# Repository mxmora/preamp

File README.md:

# preamp
Guitar buffer preamp

Added buffer input front end
Added more mounting holes

Version 1.1.4 only has the channel A clean section.
Version 1.1.4 has been built and tested and works with no error. Four minor errors were corrected and new boards were made.

Added Distortion Section
changed version to 1.2.0

This now has an A/B section A for clean and B for Lead Channel. 

Added LED for channel B indicator.

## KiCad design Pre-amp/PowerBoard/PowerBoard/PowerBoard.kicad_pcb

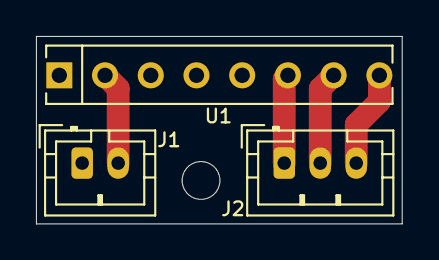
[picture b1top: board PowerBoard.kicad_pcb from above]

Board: 2 copper layers, 20.3 x 10.4 mm, 4 parts (0 on the bottom side), 5 nets.

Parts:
H1: MountingHole; MountingHole_2.1mm
J1: Conn_01x02_Male; JST_PH_B2B-PH-K_1x02_P2.00mm_Vertical
J2: Conn_01x03_Male; JST_PH_B3B-PH-K_1x03_P2.00mm_Vertical
U1: DPAN02; SIP-8_19x3mm_P2.54mm

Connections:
+9V: J1.2, U1.2
+15V: J2.1, U1.6
-15V: J2.3, U1.8
GND: J1.1, U1.1
unnamed: J2.2, U1.7

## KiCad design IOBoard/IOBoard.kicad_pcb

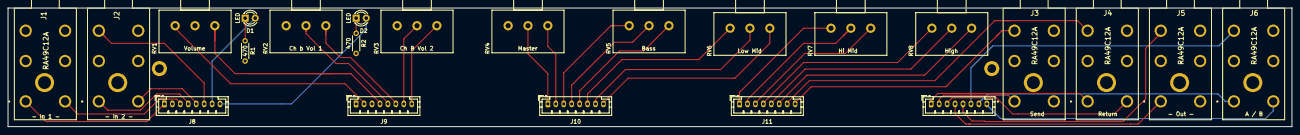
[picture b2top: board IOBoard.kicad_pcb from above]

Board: 2 copper layers, 323.2 x 29.8 mm, 25 parts (0 on the bottom side), 40 nets.

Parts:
D1, D2: LED; LED_D3.0mm
H1, H2: MountingHole_Pad; MountingHole_2.2mm_M2_DIN965_Pad
J1, J2, J3, J4, J5, J6: RA49C12A; RA49C14B
J7, J8, J9, J10, J11: Conn_01x08_Male; JST_PH_B8B-PH-K_1x08_P2.00mm_Vertical
R1, R2: 470; R_Axial_DIN0204_L3.6mm_D1.6mm_P5.08mm_Horizontal
RV1: Volume; Potentiometer_Alps_RK163_Single_Horizontal
RV2: Ch b Vol 1; Potentiometer_Alps_RK163_Single_Horizontal
RV3: Ch B Vol 2; Potentiometer_Alps_RK163_Single_Horizontal
RV4: Master; Potentiometer_Alps_RK163_Single_Horizontal
RV5: Bass; Potentiometer_Alps_RK163_Single_Horizontal
RV6: Low Mid; Potentiometer_Alps_RK163_Single_Horizontal
RV7: Hi Mid; Potentiometer_Alps_RK163_Single_Horizontal
RV8: High; Potentiometer_Alps_RK163_Single_Horizontal

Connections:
GND: H1.1, H2.1, J1.5, J8.2, J9.3, R1.2, R2.2, RV1.2, RV2.3, RV3.3, RV4.3
unnamed: D1.1, R1.1
unnamed: D1.2, J8.7
unnamed: D2.1, R2.1
unnamed: D2.2, J8.8
unnamed: J1.1, J8.1
unnamed: J1.2, J8.3
unnamed: J2.1, J8.4
unnamed: J2.2, J8.5
unnamed: J2.5, J8.6
unnamed: J3.1, J7.2
unnamed: J4.1, J7.1
unnamed: J4.2, J7.3
unnamed: J5.1, J7.4
unnamed: J5.5, J7.5
unnamed: J6.1, J7.7
unnamed: J6.2, J7.8
unnamed: J6.5, J7.6
unnamed: J9.2, RV1.3
unnamed: J9.4, RV1.1
unnamed: J9.5, RV2.2
unnamed: J9.6, RV2.1
unnamed: J9.7, RV3.2
unnamed: J9.8, RV3.1
unnamed: J10.1, RV4.2
unnamed: J10.2, RV4.1
unnamed: J10.3, RV5.3
unnamed: J10.4, RV5.2
unnamed: J10.5, RV5.1
unnamed: J10.6, RV6.3
unnamed: J10.7, RV6.2
unnamed: J10.8, RV6.1
unnamed: J11.1, RV7.3
unnamed: J11.2, RV7.2
unnamed: J11.3, RV7.1
unnamed: J11.4, RV8.3
unnamed: J11.5, RV8.2
unnamed: J11.6, RV8.1
unnamed: J4.5, J11.7
unnamed: J3.5, J11.8

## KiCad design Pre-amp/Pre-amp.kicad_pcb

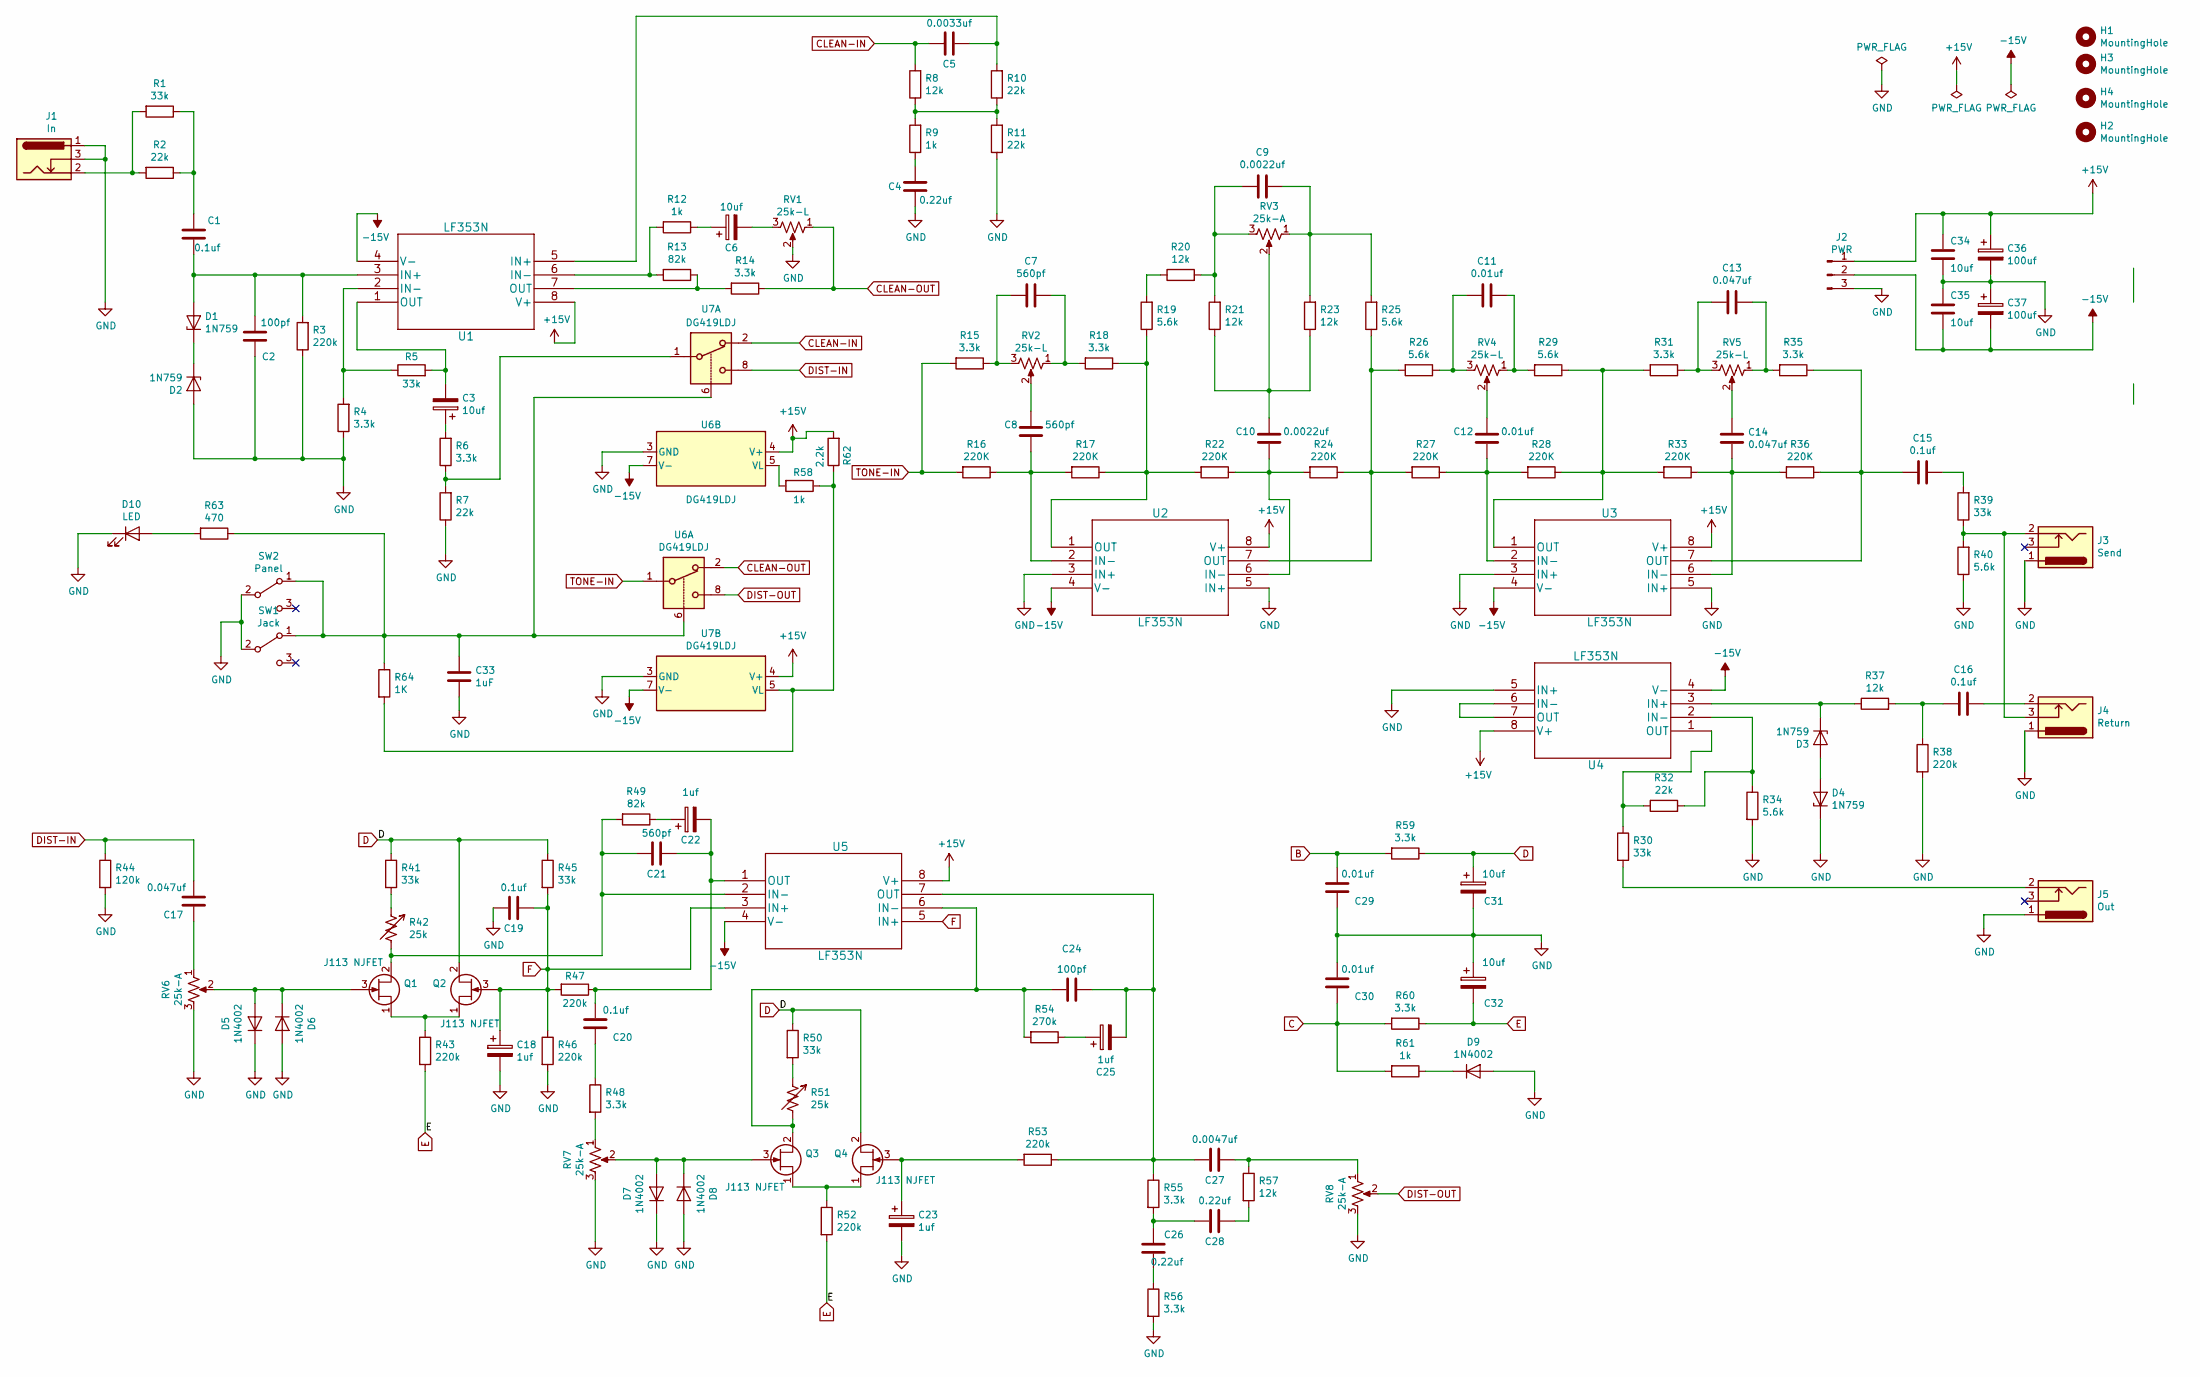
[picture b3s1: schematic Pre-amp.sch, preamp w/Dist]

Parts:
C1, C15, C16, C19, C20: 0.1uf; C_Disc_D3.8mm_W2.6mm_P2.50mm
C2, C24: 100pf; C_Disc_D3.8mm_W2.6mm_P2.50mm
C3, C6, C31, C32: 10uf; CP_Radial_D4.0mm_P1.50mm
C4, C26, C28: 0.22uf; C_Disc_D3.8mm_W2.6mm_P2.50mm
C5: 0.0033uf; C_Disc_D3.8mm_W2.6mm_P2.50mm
C7, C8, C21: 560pf; C_Disc_D3.8mm_W2.6mm_P2.50mm
C9, C10: 0.0022uf; C_Disc_D3.8mm_W2.6mm_P2.50mm
C11, C12, C29, C30: 0.01uf; C_Disc_D3.8mm_W2.6mm_P2.50mm
C13, C14, C17: 0.047uf; C_Disc_D3.8mm_W2.6mm_P2.50mm
C18, C22, C23, C25: 1uf; CP_Radial_D4.0mm_P1.50mm
C27: 0.0047uf; C_Disc_D3.8mm_W2.6mm_P2.50mm
C33: 1uF; C_Rect_L7.0mm_W2.0mm_P5.00mm
C34, C35: 10uf; C_Disc_D6.0mm_W2.5mm_P5.00mm
C36, C37: 100uf; CP_Radial_D8.0mm_P5.00mm
D1, D2, D3, D4: 1N759; D_DO-35_SOD27_P7.62mm_Horizontal
D5, D6, D7, D8, D9: 1N4002; D_DO-41_SOD81_P7.62mm_Horizontal
D10: LED; PinHeader_2x01_P2.00mm_Vertical
H1, H2, H3, H4: MountingHole; MountingHole_2.2mm_M2_DIN965_Pad
J1: In; PinHeader_1x03_P2.00mm_Vertical
J2: PWR; PinHeader_1x03_P2.00mm_Vertical
J3: Send; PinHeader_1x03_P2.00mm_Vertical
J4: Return; PinHeader_1x03_P2.00mm_Vertical
J5: Out; PinHeader_1x03_P2.00mm_Vertical
Q1, Q2, Q3, Q4: J113 NJFET; TO-92
R1, R5, R30, R39, R41, R45, R50: 33k; R_Axial_DIN0204_L3.6mm_D1.6mm_P5.08mm_Horizontal
R2, R7, R10, R11, R32: 22k; R_Axial_DIN0204_L3.6mm_D1.6mm_P5.08mm_Horizontal
R3, R38, R43, R46, R47, R52, R53: 220k; R_Axial_DIN0204_L3.6mm_D1.6mm_P5.08mm_Horizontal
R4, R6, R14, R15, R18, R31, R35, R48, R55, R56, R59, R60: 3.3k; R_Axial_DIN0204_L3.6mm_D1.6mm_P5.08mm_Horizontal
R8, R20, R21, R23, R37, R57: 12k; R_Axial_DIN0204_L3.6mm_D1.6mm_P5.08mm_Horizontal
R9, R12, R58, R61: 1k; R_Axial_DIN0204_L3.6mm_D1.6mm_P5.08mm_Horizontal
R13, R49: 82k; R_Axial_DIN0204_L3.6mm_D1.6mm_P5.08mm_Horizontal
R16, R17, R22, R24, R27, R28, R33, R36: 220K; R_Axial_DIN0204_L3.6mm_D1.6mm_P5.08mm_Horizontal
R19, R25, R26, R29, R34, R40: 5.6k; R_Axial_DIN0204_L3.6mm_D1.6mm_P5.08mm_Horizontal
R42, R51: 25k; Potentiometer_Bourns_3386F_Vertical
R44: 120k; R_Axial_DIN0204_L3.6mm_D1.6mm_P5.08mm_Horizontal
R54: 270k; R_Axial_DIN0204_L3.6mm_D1.6mm_P5.08mm_Horizontal
R62: 2.2k; R_Axial_DIN0204_L3.6mm_D1.6mm_P5.08mm_Horizontal
R63: 470; R_Axial_DIN0204_L3.6mm_D1.6mm_P5.08mm_Horizontal
R64: 1K; R_Axial_DIN0204_L3.6mm_D1.6mm_P5.08mm_Horizontal
RV1, RV2, RV4, RV5: 25k-L; Potentiometer_Alps_RK163_Single_Vertical
RV3, RV6, RV7, RV8: 25k-A; Potentiometer_Alps_RK163_Single_Vertical
SW1: Jack; Pin_Header_Straight_1x03_Pitch2.00mm
SW2: Panel; Pin_Header_Straight_1x03_Pitch2.00mm
U1, U2, U3, U4, U5: LF353N; DIP-8_W7.62mm_LongPads
U6, U7: DG419LDJ; DIP-8_W7.62mm_LongPads

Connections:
+15V: C34.1, C36.1, J2.1, R62.2, U1.8 (V+), U2.8 (V+), U3.8 (V+), U4.8 (V+), U5.8 (V+), U6.4 (V+), U7.4 (V+)
-15V: C35.2, C37.2, J2.2, U1.4 (V-), U2.4 (V-), U3.4 (V-), U4.4 (V-), U5.4 (V-), U6.7 (V-), U7.7 (V-)
B: C29.1, R59.2
C: C30.2, R60.2, R61.2
CLEAN-IN: C5.1, R8.2, U7.2
CLEAN-OUT: R14.1, RV1.1, U6.2
D: C31.1, Q2.2 (D), Q4.2 (D), R41.1, R45.1, R50.1, R59.1
DIST-IN: C17.1, R44.1, U7.8
DIST-OUT: RV8.2, U6.8
E: C32.2, R43.2, R52.2, R60.1
F: C18.1, C19.1, Q2.3 (G), R45.2, R46.1, R47.2, U5.3 (IN+), U5.5 (IN+)
GND: C2.1, C4.2, C18.2, C19.2, C23.2, C29.2, C30.1, C31.2, C32.1, C33.2, C34.2, C35.1, C36.2, C37.1, D2.2 (A), D4.1 (K), D5.1 (K), D6.2 (A), D7.1 (K), D8.2 (A), D9.2 (A), D10.1 (K), J1.1, J1.3, J2.3, J3.1, J4.1, J5.1, R3.1, R4.1, R7.1, R11.1, R34.2, R38.2, R40.1, R44.2, R46.2, R56.2, RV1.2, RV6.3, RV7.3, RV8.3, SW1.2 (B), SW2.2 (B), U2.3 (IN+), U2.5 (IN+), U3.3 (IN+), U3.5 (IN+), U4.5 (IN+), U6.3 (GND), U7.3 (GND)
unnamed: C1.1, C2.2, D1.2 (A), R3.2, U1.3 (IN+)
unnamed: C1.2, R1.1, R2.1
unnamed: C3.1, R6.2
unnamed: C3.2, R5.2, U1.1 (OUT)
unnamed: C4.1, R9.1
unnamed: C5.2, R10.2, U1.5 (IN+)
unnamed: C6.1, R12.1
unnamed: C6.2, RV1.3
unnamed: C7.1, R18.2, RV2.1
unnamed: C7.2, R15.1, RV2.3
unnamed: C8.1, RV2.2
unnamed: C8.2, R16.1, R17.2, U2.2 (IN-)
unnamed: C9.1, R23.2, R25.2, RV3.1
unnamed: C9.2, R20.2, R21.2, RV3.3
unnamed: C10.1, R21.1, R23.1, RV3.2
unnamed: C10.2, R22.1, R24.2, U2.6 (IN-)
unnamed: C11.1, R29.2, RV4.1
unnamed: C11.2, R26.1, RV4.3
unnamed: C12.1, RV4.2
unnamed: C12.2, R27.1, R28.2, U3.2 (IN-)
unnamed: C13.1, R35.2, RV5.1
unnamed: C13.2, R31.1, RV5.3
unnamed: C14.1, RV5.2
unnamed: C14.2, R33.1, R36.2, U3.6 (IN-)
unnamed: C15.1, R39.2
unnamed: C15.2, R35.1, R36.1, U3.7 (OUT)
unnamed: C16.1, J4.2
unnamed: C16.2, R37.2, R38.1
unnamed: C17.2, RV6.1
unnamed: C20.1, C21.1, C22.2, R47.1, U5.1 (OUT)
unnamed: C20.2, R48.1
unnamed: C21.2, Q1.2 (D), R42.2, R49.2, U5.2 (IN-)
unnamed: C22.1, R49.1
unnamed: C23.1, Q4.3 (G), R53.2
unnamed: C24.1, C25.2, C27.1, R53.1, R55.1, U5.7 (OUT)
unnamed: C24.2, Q3.2 (D), R51.2, R54.2, U5.6 (IN-)
unnamed: C25.1, R54.1
unnamed: C26.1, R56.1
unnamed: C26.2, C28.1, R55.2
unnamed: C27.2, R57.1, RV8.1
unnamed: C28.2, R57.2
unnamed: C33.1, R63.1, R64.1, SW1.1 (A), SW2.1 (A), U6.6, U7.6
unnamed: D1.1 (K), D2.1 (K)
unnamed: D3.1 (K), R37.1, U4.3 (IN+)
unnamed: D3.2 (A), D4.2 (A)
unnamed: D5.2 (A), D6.1 (K), Q1.3 (G), RV6.2
unnamed: D7.2 (A), D8.1 (K), Q3.3 (G), RV7.2
unnamed: D9.1 (K), R61.1
unnamed: D10.2 (A), R63.2
unnamed: J1.2, R1.2, R2.2
unnamed: J3.2, J4.3, R39.1, R40.2
unnamed: J5.2, R30.2
unnamed: Q1.1 (S), Q2.1 (S), R43.1
unnamed: Q3.1 (S), Q4.1 (S), R52.1
unnamed: R4.2, R5.1, U1.2 (IN-)
unnamed: R6.1, R7.2, U7.1
unnamed: R8.1, R9.2, R10.1, R11.2
unnamed: R12.2, R13.2, U1.6 (IN-)
unnamed: R13.1, R14.2, U1.7 (OUT)
unnamed: R17.1, R18.1, R19.1, R22.2, U2.1 (OUT)
unnamed: R19.2, R20.1
unnamed: R24.1, R25.1, R26.2, R27.2, U2.7 (OUT)
unnamed: R28.1, R29.1, R31.2, R33.2, U3.1 (OUT)
unnamed: R30.1, R32.1, U4.1 (OUT)
unnamed: R32.2, R34.1, U4.2 (IN-)
unnamed: R41.2, R42.1
unnamed: R48.2, RV7.1
unnamed: R50.2, R51.1
unnamed: R58.1, R62.1, R64.2, U7.5 (VL)
unnamed: R58.2, U6.5 (VL)
unnamed: U4.6 (IN-), U4.7 (OUT)
TONE-IN: R15.2, R16.2, U6.1

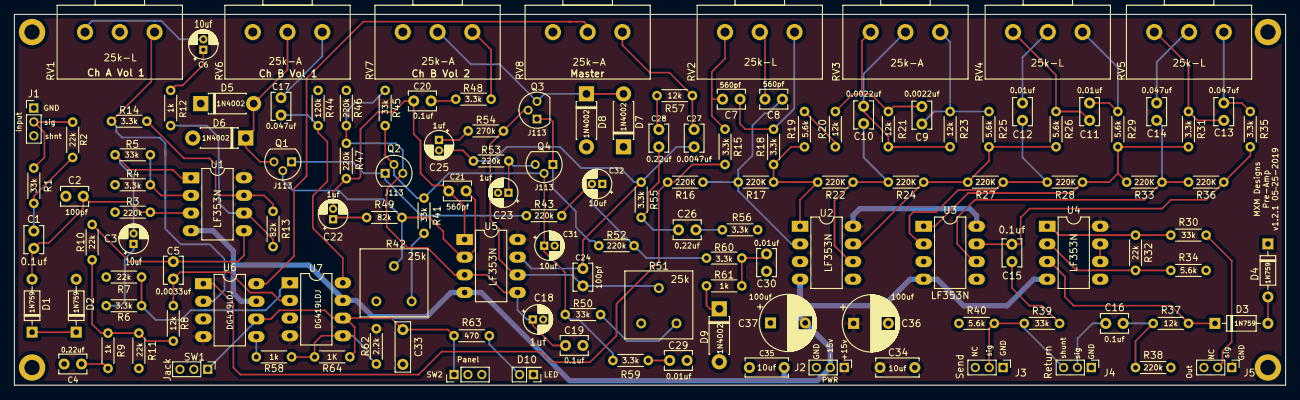
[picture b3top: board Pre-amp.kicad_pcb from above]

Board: 2 copper layers, 182.9 x 53.3 mm, 141 parts (0 on the bottom side), 84 nets.

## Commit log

2019-04-01 Add buffer input to pre-amp
2019-04-02 update version
2019-04-02 update layout move vaules to silkscreen layer. Change some routes to give more room around pads.
2019-04-02 update to pc mount pots
2019-04-19 add switching
2019-04-28 Fix errors found in build. Change version to 1.2.0
2019-04-30 update schematic symbols
2019-05-01 update schematic for distortion section
2019-05-01 place all components
2019-05-01 get all parts on the board
2019-05-06 update the schematic and PCB for lead section.
2019-05-07 connect all traces
2019-05-07 small updates
2019-05-07 add bom
2019-05-07 add more files
2019-05-07 clean up PCB
2019-05-09 fx botch git commits
2019-05-09 spread out components better.
2019-05-09 remove the .DSStore file
2019-05-10 update PCB
2019-05-12 tweak PCB layout
2019-05-12 add power caps
2019-05-14 Rearrange the board for taller things to be away from the edges.
2019-05-15 Add IOBoard
2019-05-15 add jacks
2019-05-16 split connectors and reflow
2019-05-26 fix 1uf caps to CP
2019-05-29 move to the same size connectors
2019-05-30 add power convertor board
